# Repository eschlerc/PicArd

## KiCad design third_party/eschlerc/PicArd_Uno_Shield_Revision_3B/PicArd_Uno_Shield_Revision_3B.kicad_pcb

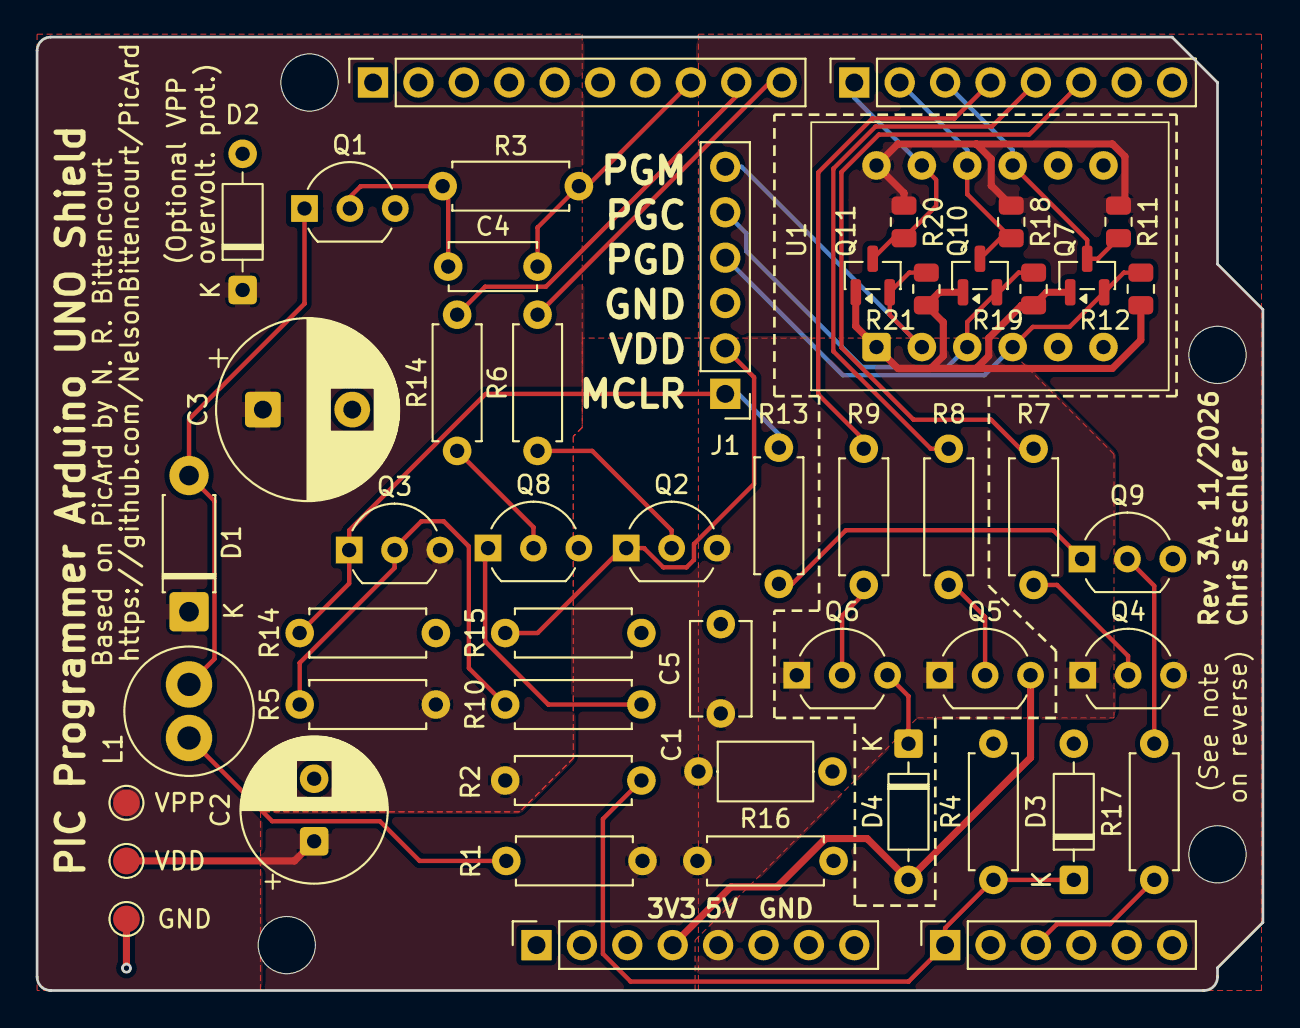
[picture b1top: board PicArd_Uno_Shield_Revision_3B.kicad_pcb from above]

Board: 2 copper layers, 68.6 x 53.3 mm, 56 parts (0 on the bottom side), 34 nets.

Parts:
C1: 100nF; C_Axial_L5.1mm_D3.1mm_P7.50mm_Horizontal
C2: 470uF; CP_Radial_D8.0mm_P3.50mm
C3: 47uF; CP_Radial_D10.0mm_P5.00mm
C4: 1nF; C_Disc_D4.7mm_W2.5mm_P5.00mm
C5: 10uF; C_Disc_D5.1mm_W3.2mm_P5.00mm
D1: 1N5817; D_DO-41_SOD81_P7.62mm_Horizontal
D2: ZPD13; D_DO-35_SOD27_P7.62mm_Horizontal
D3: TZX5V1A; D_DO-35_SOD27_P7.62mm_Horizontal
D4: 1N4148; D_DO-35_SOD27_P7.62mm_Horizontal
J1: ICSP; PinHeader_1x06_P2.54mm_Vertical
J2: Digital/PWM; PinSocket_1x10_P2.54mm_Vertical
J3: Power; PinSocket_1x08_P2.54mm_Vertical
J4: Analog; PinSocket_1x06_P2.54mm_Vertical
J5: Digital/PWM; PinSocket_1x08_P2.54mm_Vertical
L1: 2.2mH; L_Radial_D7.0mm_P3.00mm
MH1, MH2, MH3, MH4: MountingHole_3.2mm
Q1, Q8, Q9: BC547; TO-92_Inline_Wide
Q2, Q3, Q4, Q5, Q6: BC557; TO-92_Inline_Wide
Q7, Q10, Q11: BSS138; SOT-23
R1: 56R; R_Axial_DIN0207_L6.3mm_D2.5mm_P7.62mm_Horizontal
R2: 4k7 1%; R_Axial_DIN0207_L6.3mm_D2.5mm_P7.62mm_Horizontal
R3: 1k2; R_Axial_DIN0207_L6.3mm_D2.5mm_P7.62mm_Horizontal
R4: 2k8 1%; R_Axial_DIN0207_L6.3mm_D2.5mm_P7.62mm_Horizontal
R5: 100k; R_Axial_DIN0207_L6.3mm_D2.5mm_P7.62mm_Horizontal
R6, R14#2: 4k7; R_Axial_DIN0207_L6.3mm_D2.5mm_P7.62mm_Horizontal
R7, R8, R9: 2k2; R_Axial_DIN0207_L6.3mm_D2.5mm_P7.62mm_Horizontal
R10, R14, R15, R16, R17: 10k; R_Axial_DIN0207_L6.3mm_D2.5mm_P7.62mm_Horizontal
R11, R12, R18, R19, R20, R21: 27k; R_0805_2012Metric
R13: 220R; R_Axial_DIN0207_L6.3mm_D2.5mm_P7.62mm_Horizontal
TP1: VPP; TestPoint_Pad_D1.5mm
TP2: VDD; TestPoint_Pad_D1.5mm
TP3: GND; TestPoint_Pad_D1.5mm
U1: Adafruit 757; DIP-12_W10.16mm

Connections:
+3V3: D4.2 (A), J3.4, Q5.3 (E)
+5V: J3.5, Q4.3 (E), R11.1, R18.1, R20.1, U1.12 (HV)
GND: C1.2, C2.2, C3.2, C5.2, D2.2 (A), D3.2 (A), J1.3, J2.4, J3.6, J3.7, Q1.3 (E), Q8.3 (E), Q9.3 (E), R4.2, R14.2, R15.2, R16.2, TP3.1 (1_1), U1.6 (GND), U1.7 (GND)
ICSP_AUX: J5.1, Q11.3 (D), R20.2, U1.11 (B1)
ICSP_AUX_DEV: J1.6, Q11.2 (S), R21.2, U1.2 (A1)
ICSP_CLOCK: J5.2, Q10.3 (D), R18.2, U1.10 (B2)
ICSP_CLOCK_DEV: J1.5, Q10.2 (S), R19.2, U1.3 (A2)
ICSP_DATA: J5.3, Q7.3 (D), R11.2, U1.9 (B3)
ICSP_DATA_DEV: J1.4, Q7.2 (S), R12.2, U1.4 (A3)
MCLR_ONOFF: J4.3, R17.1
unnamed: D1.2 (A), L1.2, Q1.1 (C)
unnamed: D4.1 (K), Q6.3 (E)
unnamed: L1.1, R1.2
unnamed: C4.2, Q1.2 (B), R3.2
unnamed: Q2.2 (B), R6.2
unnamed: Q3.2 (B), R5.2, R10.1
unnamed: Q4.2 (B), R7.2
unnamed: Q5.2 (B), R8.2
unnamed: Q6.2 (B), R9.2
unnamed: Q8.2 (B), R14#2.2
unnamed: Q8.1 (C), R10.2
unnamed: Q9.2 (B), R17.2
unnamed: Q9.1 (C), R13.2
PWM: C4.1, J2.8, R3.1
PWM_FB: D3.1 (K), J4.1, R2.2, R4.1
VDD: C1.1, C2.1, C5.1, Q2.3 (E), Q4.1 (C), Q5.1 (C), Q6.1 (C), Q7.1 (G), Q10.1 (G), Q11.1 (G), R1.1, R12.1, R16.1, R19.1, R21.1, TP2.1 (1_1), U1.1 (LV)
VDD_2V7: J5.4, R9.1
VDD_3V3: J5.5, R8.1
VDD_5V: J5.6, R7.1
VDD_DEV: J1.2, Q2.1 (C), R15.1
VDD_ONOFF: J2.10, R6.1
VPP: C3.1, D1.1 (K), D2.1 (K), Q3.3 (E), R2.1, R5.1, TP1.1 (1_1)
VPP_DEV: J1.1, Q3.1 (C), R13.1, R14.1
VPP_ONOFF: J2.9, R14#2.1
